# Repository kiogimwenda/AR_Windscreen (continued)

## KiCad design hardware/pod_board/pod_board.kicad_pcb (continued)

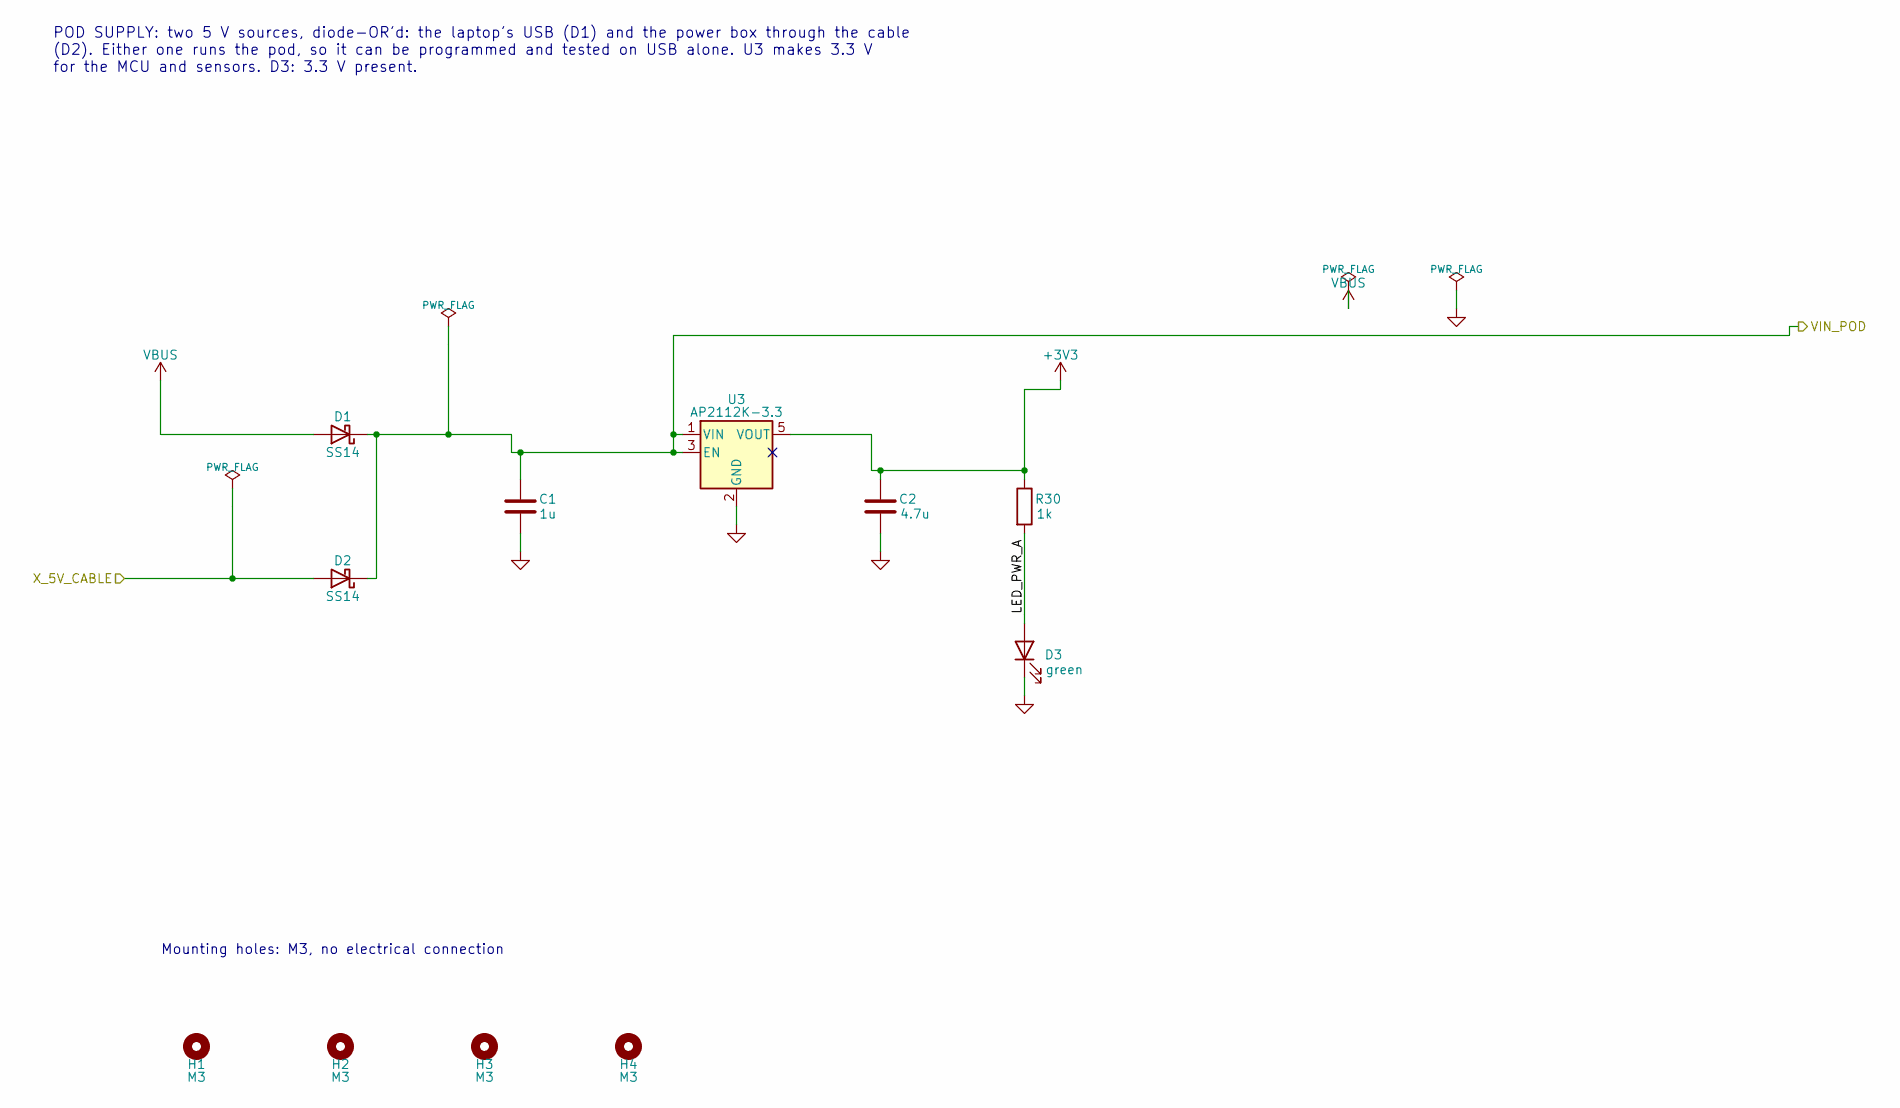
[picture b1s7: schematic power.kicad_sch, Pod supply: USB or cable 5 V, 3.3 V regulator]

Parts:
C1: 1u; C_1206_3216Metric
C2: 4.7u; C_1206_3216Metric
D1, D2: SS14; D_SMA
D3: green; LED_0805_2012Metric
H1, H2, H3, H4: M3; MountingHole_3.2mm_M3
R30: 1k; R_0805_2012Metric
U3: AP2112K-3.3; SOT-23-5

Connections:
+3V3: C2.1, R30.1, U3.5 (VOUT); also elsewhere on the board
/Pod supply: USB or cable 5 V, 3.3 V regulator/LED_PWR_A: D3.2 (A), R30.2
/VIN_POD: C1.1, D1.1 (K), D2.1 (K), U3.1 (VIN), U3.3 (EN); also elsewhere on the board
/X_5V_CABLE: D2.2 (A); also elsewhere on the board
GND: C1.2, C2.2, D3.1 (K), U3.2 (GND); also elsewhere on the board
VBUS: D1.2 (A); also elsewhere on the board

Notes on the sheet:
POD SUPPLY: two 5 V sources, diode-OR'd: the laptop's USB (D1) and the power box through the cable (D2). Either one runs the pod, so it can be programmed and tested on USB alone. U3 makes 3.3 V for the MCU and sensors. D3: 3.3 V present.
Mounting holes: M3, no electrical connection

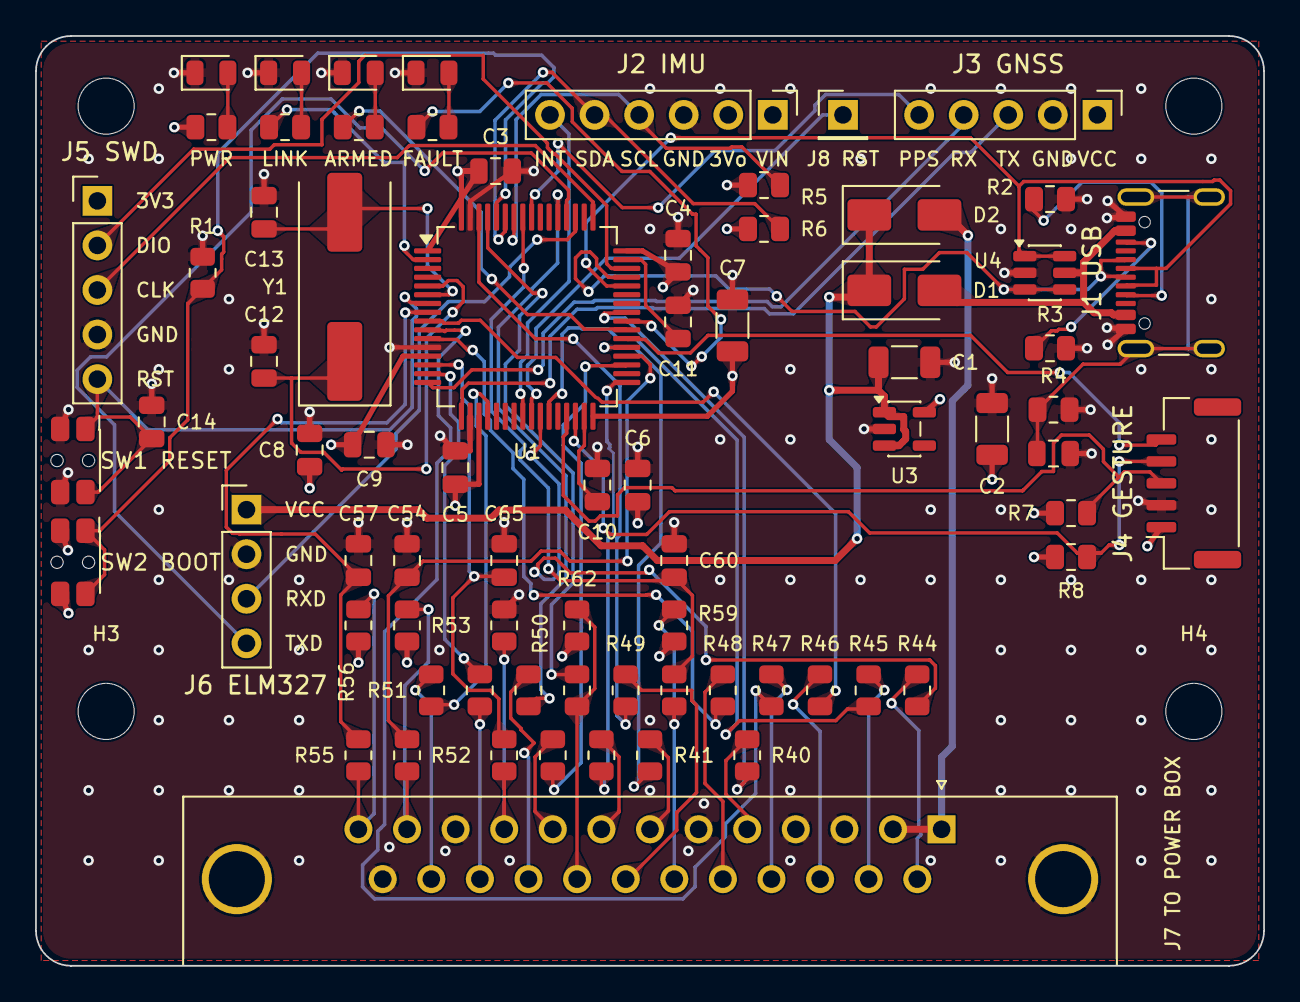
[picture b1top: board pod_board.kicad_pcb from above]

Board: 4 copper layers, 70.0 x 53.0 mm, 78 parts (0 on the bottom side), 73 nets.

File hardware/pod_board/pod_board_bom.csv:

"Reference","Value","Footprint","QUANTITY","Description"
"C1","1u","Capacitor_SMD:C_1206_3216Metric","1","1 uF, not more: USB attach inrush (hardware/sim/run_pod_supply.sh)"
"C2,C7","4.7u","Capacitor_SMD:C_1206_3216Metric","2","4.7 uF, not more: USB attach inrush (hardware/sim/run_pod_supply.sh),bulk, beside the MCU"
"C3-C6,C9,C14,C65","100n","Capacitor_SMD:C_0805_2012Metric","7","VDDA"
"C8","1u","Capacitor_SMD:C_0805_2012Metric","1","VDDA"
"C10,C11","2.2u","Capacitor_SMD:C_0805_2012Metric","2","core regulator, low-ESR ceramic"
"C12,C13","15p","Capacitor_SMD:C_0805_2012Metric","2","crystal load"
"C15","4.7n","Capacitor_SMD:C_0805_2012Metric","1",""
"C54,C57,C60","10n","Capacitor_SMD:C_0805_2012Metric","3",""
"D1,D2","SS14","Diode_SMD:D_SMA","2","+5 V from the power box into the pod's supply (diode-OR),USB VBUS into the pod's supply (diode-OR)"
"D3","green","LED_SMD:LED_0805_2012Metric","1",""
"D4","blue","LED_SMD:LED_0805_2012Metric","1",""
"D5","amber","LED_SMD:LED_0805_2012Metric","1",""
"D6","red","LED_SMD:LED_0805_2012Metric","1",""
"H1-H4","M3","MountingHole:MountingHole_3.2mm_M3","4",""
"J1","USB-C","Connector_USB:USB_C_Receptacle_GCT_USB4105-xx-A_16P_TopMnt_Horizontal","1","to the laptop: the Part 3 protocol; also powers the pod when the cable is out"
"J2","IMU (BNO085 breakout)","Connector_PinHeader_2.54mm:PinHeader_1x06_P2.54mm_Vertical","1","Adafruit 4754 JP1 row: VIN 3Vo(open) GND SCL SDA INT; mount the breakout rigidly"
"J3","GNSS (NEO-M8N breakout)","Connector_PinHeader_2.54mm:PinHeader_1x05_P2.54mm_Vertical","1","MCU GPS_TX goes to the module's RX: names are the MCU's view. Match the breakout's pin order before layout"
"J4","Gesture puck (JST-GH)","Connector_JST:JST_GH_SM05B-GHS-TB_1x05-1MP_P1.25mm_Horizontal","1","APDS-9960 on its own ~1.5 m cable, I2C2 at 100 kHz"
"J5","SWD (ST-Link)","Connector_PinHeader_2.54mm:PinHeader_1x05_P2.54mm_Vertical","1",""
"J6","ELM327 fallback (USART3)","Connector_PinHeader_2.54mm:PinHeader_1x04_P2.54mm_Vertical","1","HC-05 bridge to a Bluetooth ELM327, env:hub_elm327 only (Part 4.8.5); VCC is the pod's 5 V"
"J7","DB-25 to power box","Connector_Dsub:DSUB-25_Socket_Horizontal_P2.77x2.84mm_EdgePinOffset4.94mm_Housed_MountingHolesOffset4.94mm","1","inter-box cable, BUILD_GUIDE 4.8.3"
"J8","IMU reset (optional wire)","Connector_PinHeader_2.54mm:PinHeader_1x01_P2.54mm_Vertical","1","optional jumper to the BNO085 breakout's RST (JP2 pin 4)"
"R1,R53,R56,R59,R62","10k","Resistor_SMD:R_0805_2012Metric","5","BOOT0 low: run from flash,pull-up: the safe reading when the cable is out"
"R2,R3","5.1k","Resistor_SMD:R_0805_2012Metric","2","identifies a USB-C sink: the laptop supplies 5 V"
"R4","1M","Resistor_SMD:R_0805_2012Metric","1",""
"R5,R6","4.7k","Resistor_SMD:R_0805_2012Metric","2",""
"R7,R8","2.2k","Resistor_SMD:R_0805_2012Metric","2","stronger pull-up for the cable"
"R30-R33,R40-R48,R50-R52,R55,R58,R64","1k","Resistor_SMD:R_0805_2012Metric","19","series, DB-25 pin 12,series, DB-25 pin 13,series, DB-25 pin 14,series, DB-25 pin 15,series, DB-25 pin 16,series, DB-25 pin 17,series, DB-25 pin 18,series, DB-25 pin 19,series, DB-25 pin 22,series, DB-25 pin 24,series, DB-25 pin 5,series, DB-25 pin 7,series, DB-25 pin 8,series, DB-25 pin 9"
"R49","330","Resistor_SMD:R_0805_2012Metric","1","series, DB-25 pin 20"
"R61,R63","100","Resistor_SMD:R_0805_2012Metric","2","series, DB-25 pin 21,series, DB-25 pin 23"
"R66","100k","Resistor_SMD:R_0805_2012Metric","1","defined reading (0 V) when the cable is out; firmware ignores it then"
"SW1","RESET","Button_Switch_SMD:SW_SPST_EVQP7C","1",""
"SW2","BOOT","Button_Switch_SMD:SW_SPST_EVQP7C","1","hold at reset for the USB DFU bootloader"
"U1","STM32F405RGT6","Package_QFP:LQFP-64_10x10mm_P0.5mm","1",""
"U3","AP2112K-3.3","Package_TO_SOT_SMD:SOT-23-5","1","3.3 V, 600 mA LDO"
"U4","USBLC6-2SC6","Package_TO_SOT_SMD:SOT-23-6","1","USB ESD protection"
"Y1","8MHz","Crystal:Crystal_SMD_HC49-SD","1","HSE; firmware assumes 8 MHz (HSE_VALUE). Load caps for CL = 10 pF."

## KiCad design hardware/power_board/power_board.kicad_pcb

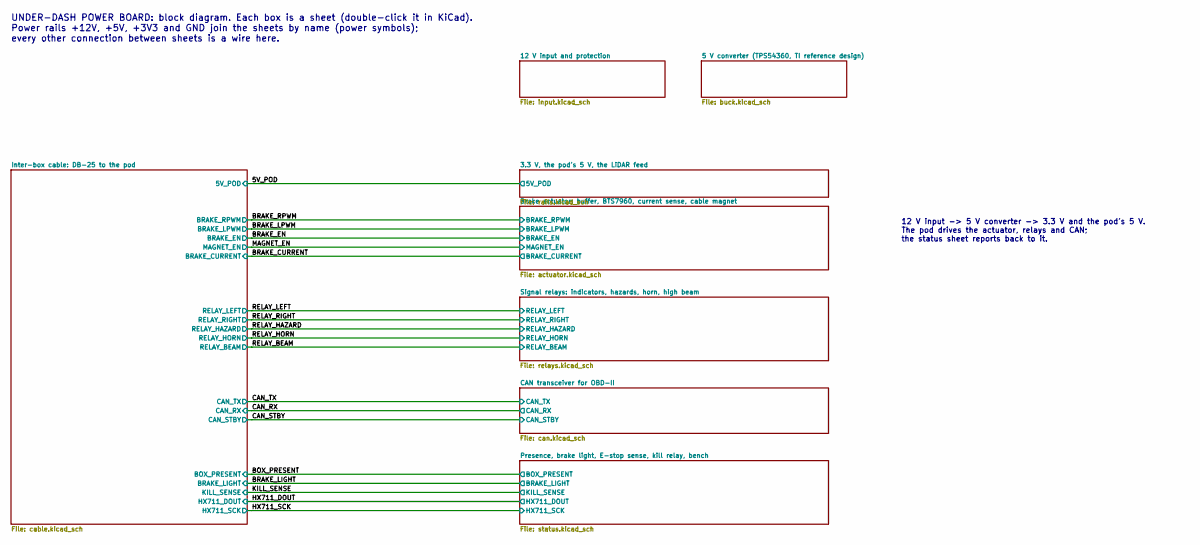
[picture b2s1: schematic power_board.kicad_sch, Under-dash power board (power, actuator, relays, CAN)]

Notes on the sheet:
UNDER-DASH POWER BOARD: block diagram. Each box is a sheet (double-click it in KiCad). Power rails +12V, +5V, +3V3 and GND join the sheets by name (power symbols); every other connection between sheets is a wire here.
12 V input -> 5 V converter -> 3.3 V and the pod's 5 V. The pod drives the actuator, relays and CAN; the status sheet reports back to it.

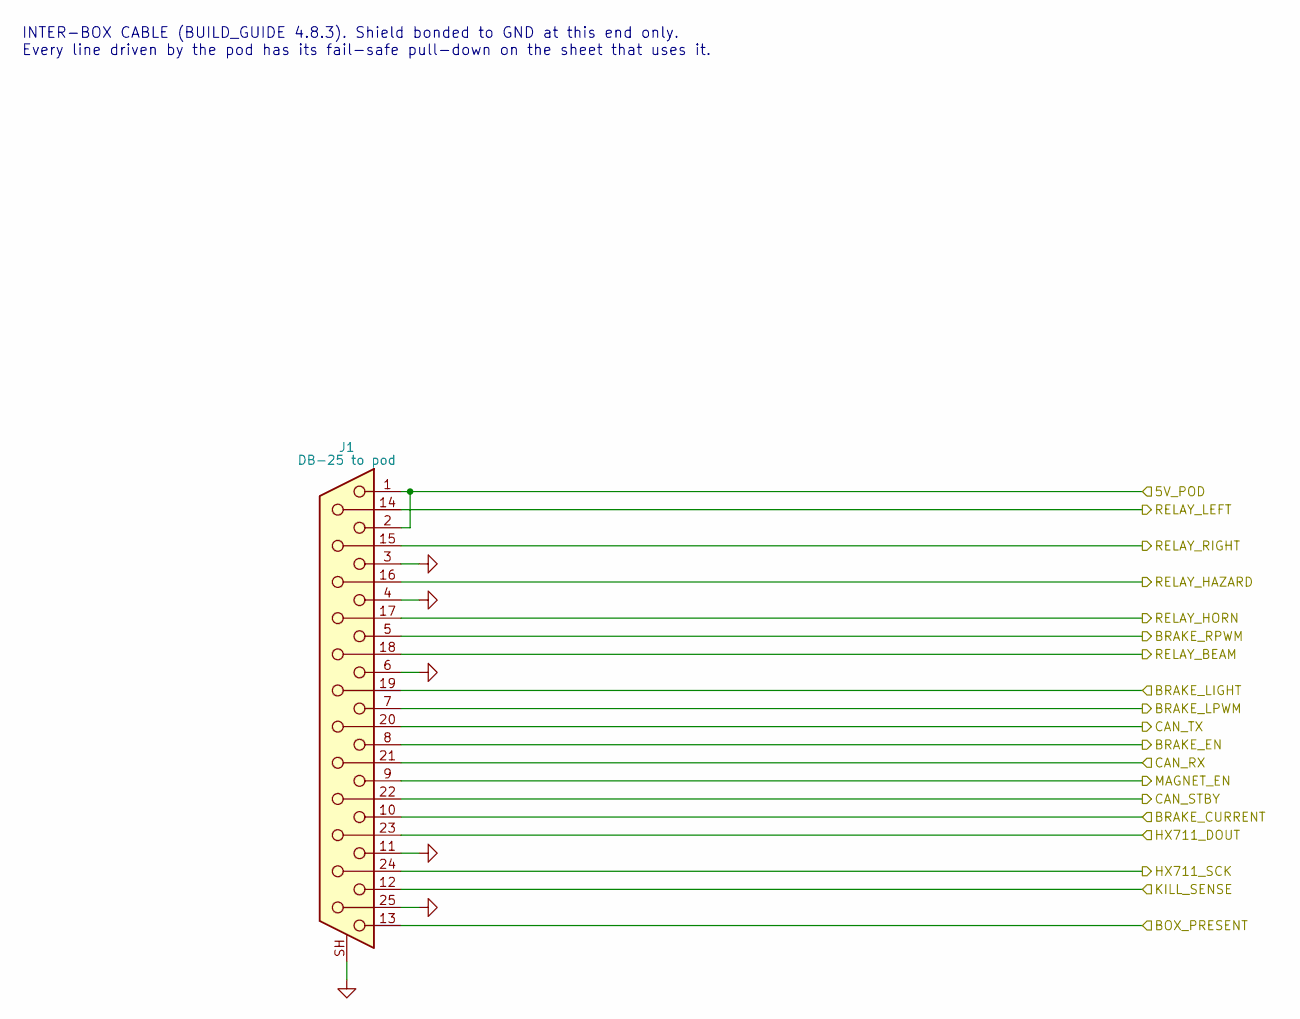
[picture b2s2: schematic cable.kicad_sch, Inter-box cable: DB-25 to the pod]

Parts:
J1: DB-25 to pod; DSUB-25_Socket_Horizontal_P2.77x2.84mm_EdgePinOffset4.94mm_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

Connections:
/5V_POD: J1.1, J1.2; also elsewhere on the board
/BOX_PRESENT: J1.13; also elsewhere on the board
/BRAKE_CURRENT: J1.10; also elsewhere on the board
/BRAKE_EN: J1.8; also elsewhere on the board
/BRAKE_LIGHT: J1.19; also elsewhere on the board
/BRAKE_LPWM: J1.7; also elsewhere on the board
/BRAKE_RPWM: J1.5; also elsewhere on the board
/CAN_RX: J1.21; also elsewhere on the board
/CAN_STBY: J1.22; also elsewhere on the board
/CAN_TX: J1.20; also elsewhere on the board
/HX711_DOUT: J1.23; also elsewhere on the board
/HX711_SCK: J1.24; also elsewhere on the board
/KILL_SENSE: J1.12; also elsewhere on the board
/MAGNET_EN: J1.9; also elsewhere on the board
/RELAY_BEAM: J1.18; also elsewhere on the board
/RELAY_HAZARD: J1.16; also elsewhere on the board
/RELAY_HORN: J1.17; also elsewhere on the board
/RELAY_LEFT: J1.14; also elsewhere on the board
/RELAY_RIGHT: J1.15; also elsewhere on the board
GND: J1.3, J1.4, J1.6, J1.11, J1.25, J1.SH (PAD); also elsewhere on the board

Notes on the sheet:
INTER-BOX CABLE (BUILD_GUIDE 4.8.3). Shield bonded to GND at this end only. Every line driven by the pod has its fail-safe pull-down on the sheet that uses it.

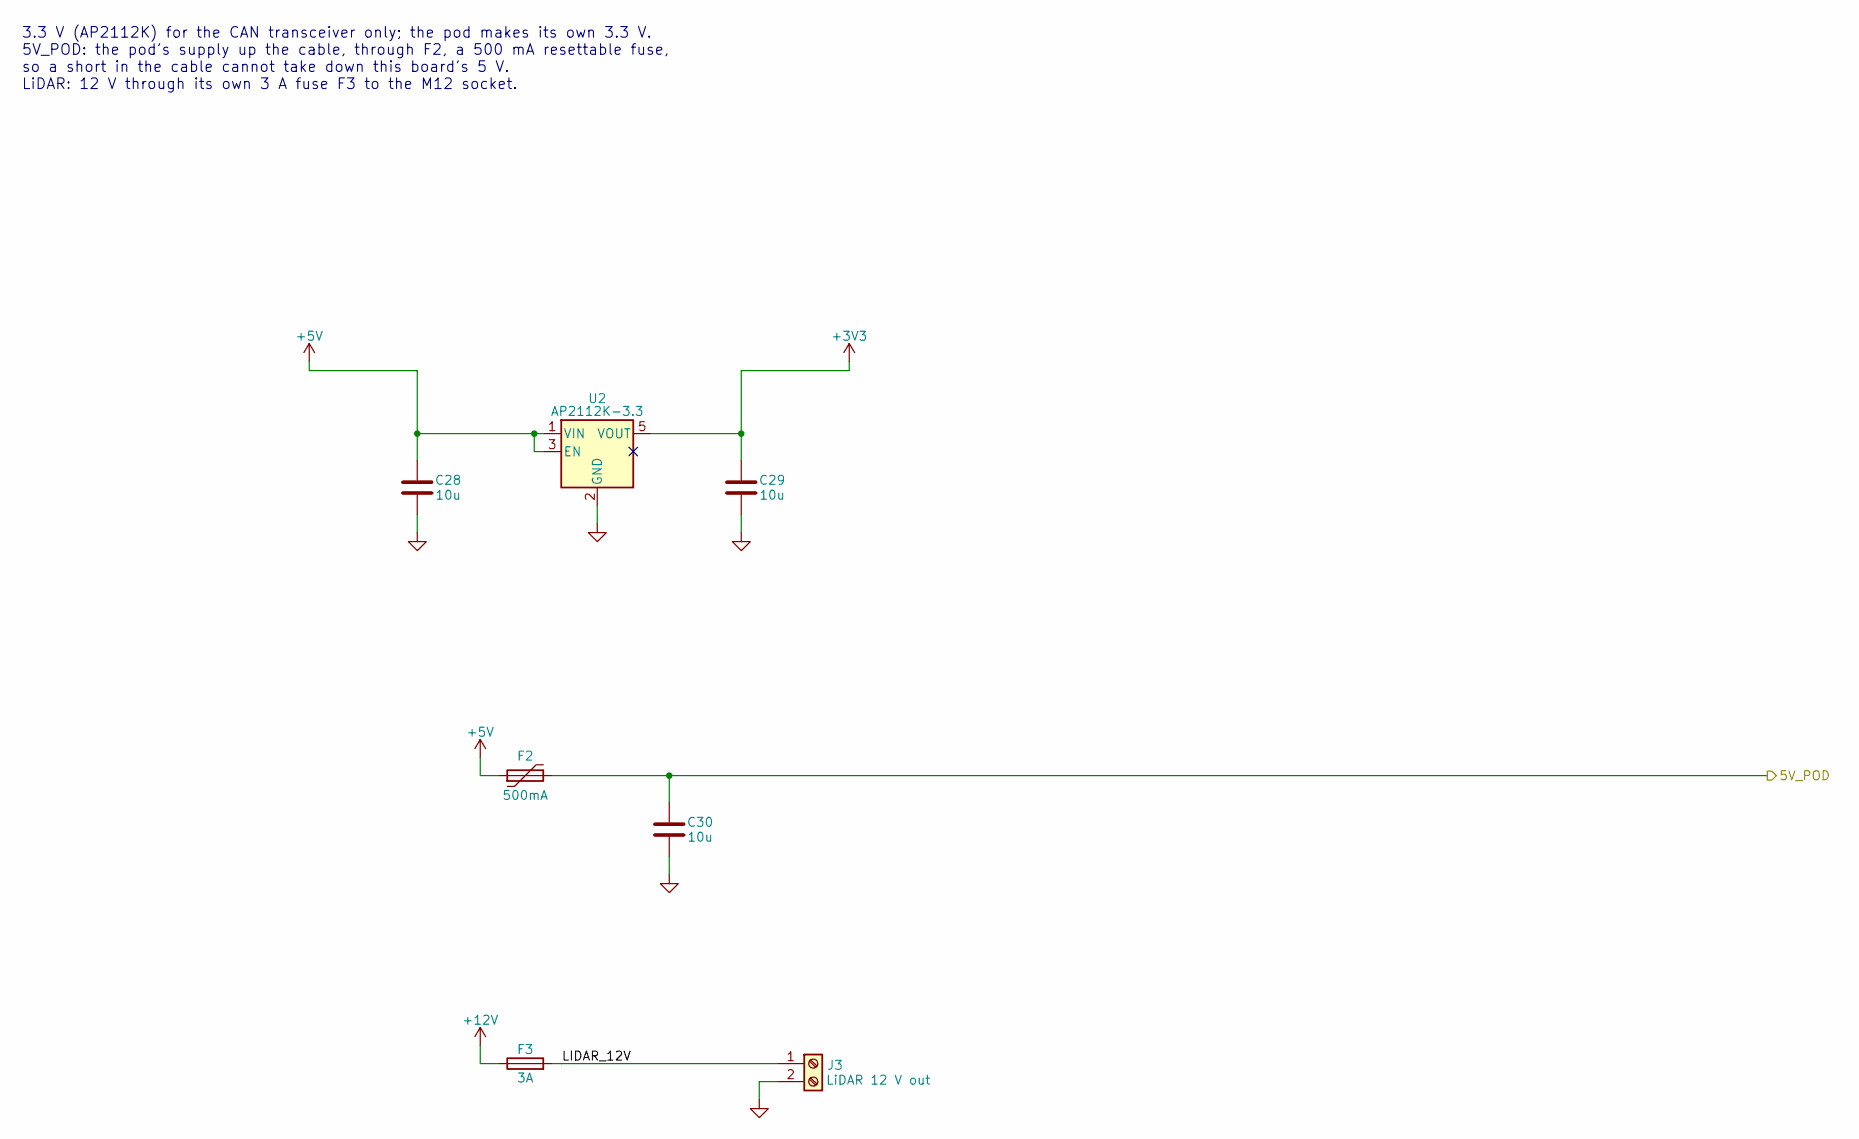
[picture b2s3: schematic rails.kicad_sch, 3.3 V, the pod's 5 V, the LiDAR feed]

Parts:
C28, C29, C30: 10u; C_1206_3216Metric
F2: 500mA; Fuse_1206_3216Metric
F3: 3A; Fuseholder_Blade_Mini_Keystone_3568
J3: LiDAR 12 V out; TerminalBlock_Phoenix_MKDS-1,5-2-5.08_1x02_P5.08mm_Horizont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
U2: AP2112K-3.3; SOT-23-5

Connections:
+3V3: C29.1, U2.5 (VOUT); also elsewhere on the board
+5V: C28.1, F2.1, U2.1 (VIN), U2.3 (EN); also elsewhere on the board
+12V: F3.1; also elsewhere on the board
/3.3 V, the pod's 5 V, the LiDAR feed/LIDAR_12V: F3.2, J3.1
/5V_POD: C30.1, F2.2; also elsewhere on the board
GND: C28.2, C29.2, C30.2, J3.2, U2.2 (GND); also elsewhere on the board

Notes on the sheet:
3.3 V (AP2112K) for the CAN transceiver only; the pod makes its own 3.3 V. 5V_POD: the pod's supply up the cable, through F2, a 500 mA resettable fuse, so a short in the cable cannot take down this board's 5 V. LiDAR: 12 V through its own 3 A fuse F3 to the M12 socket.

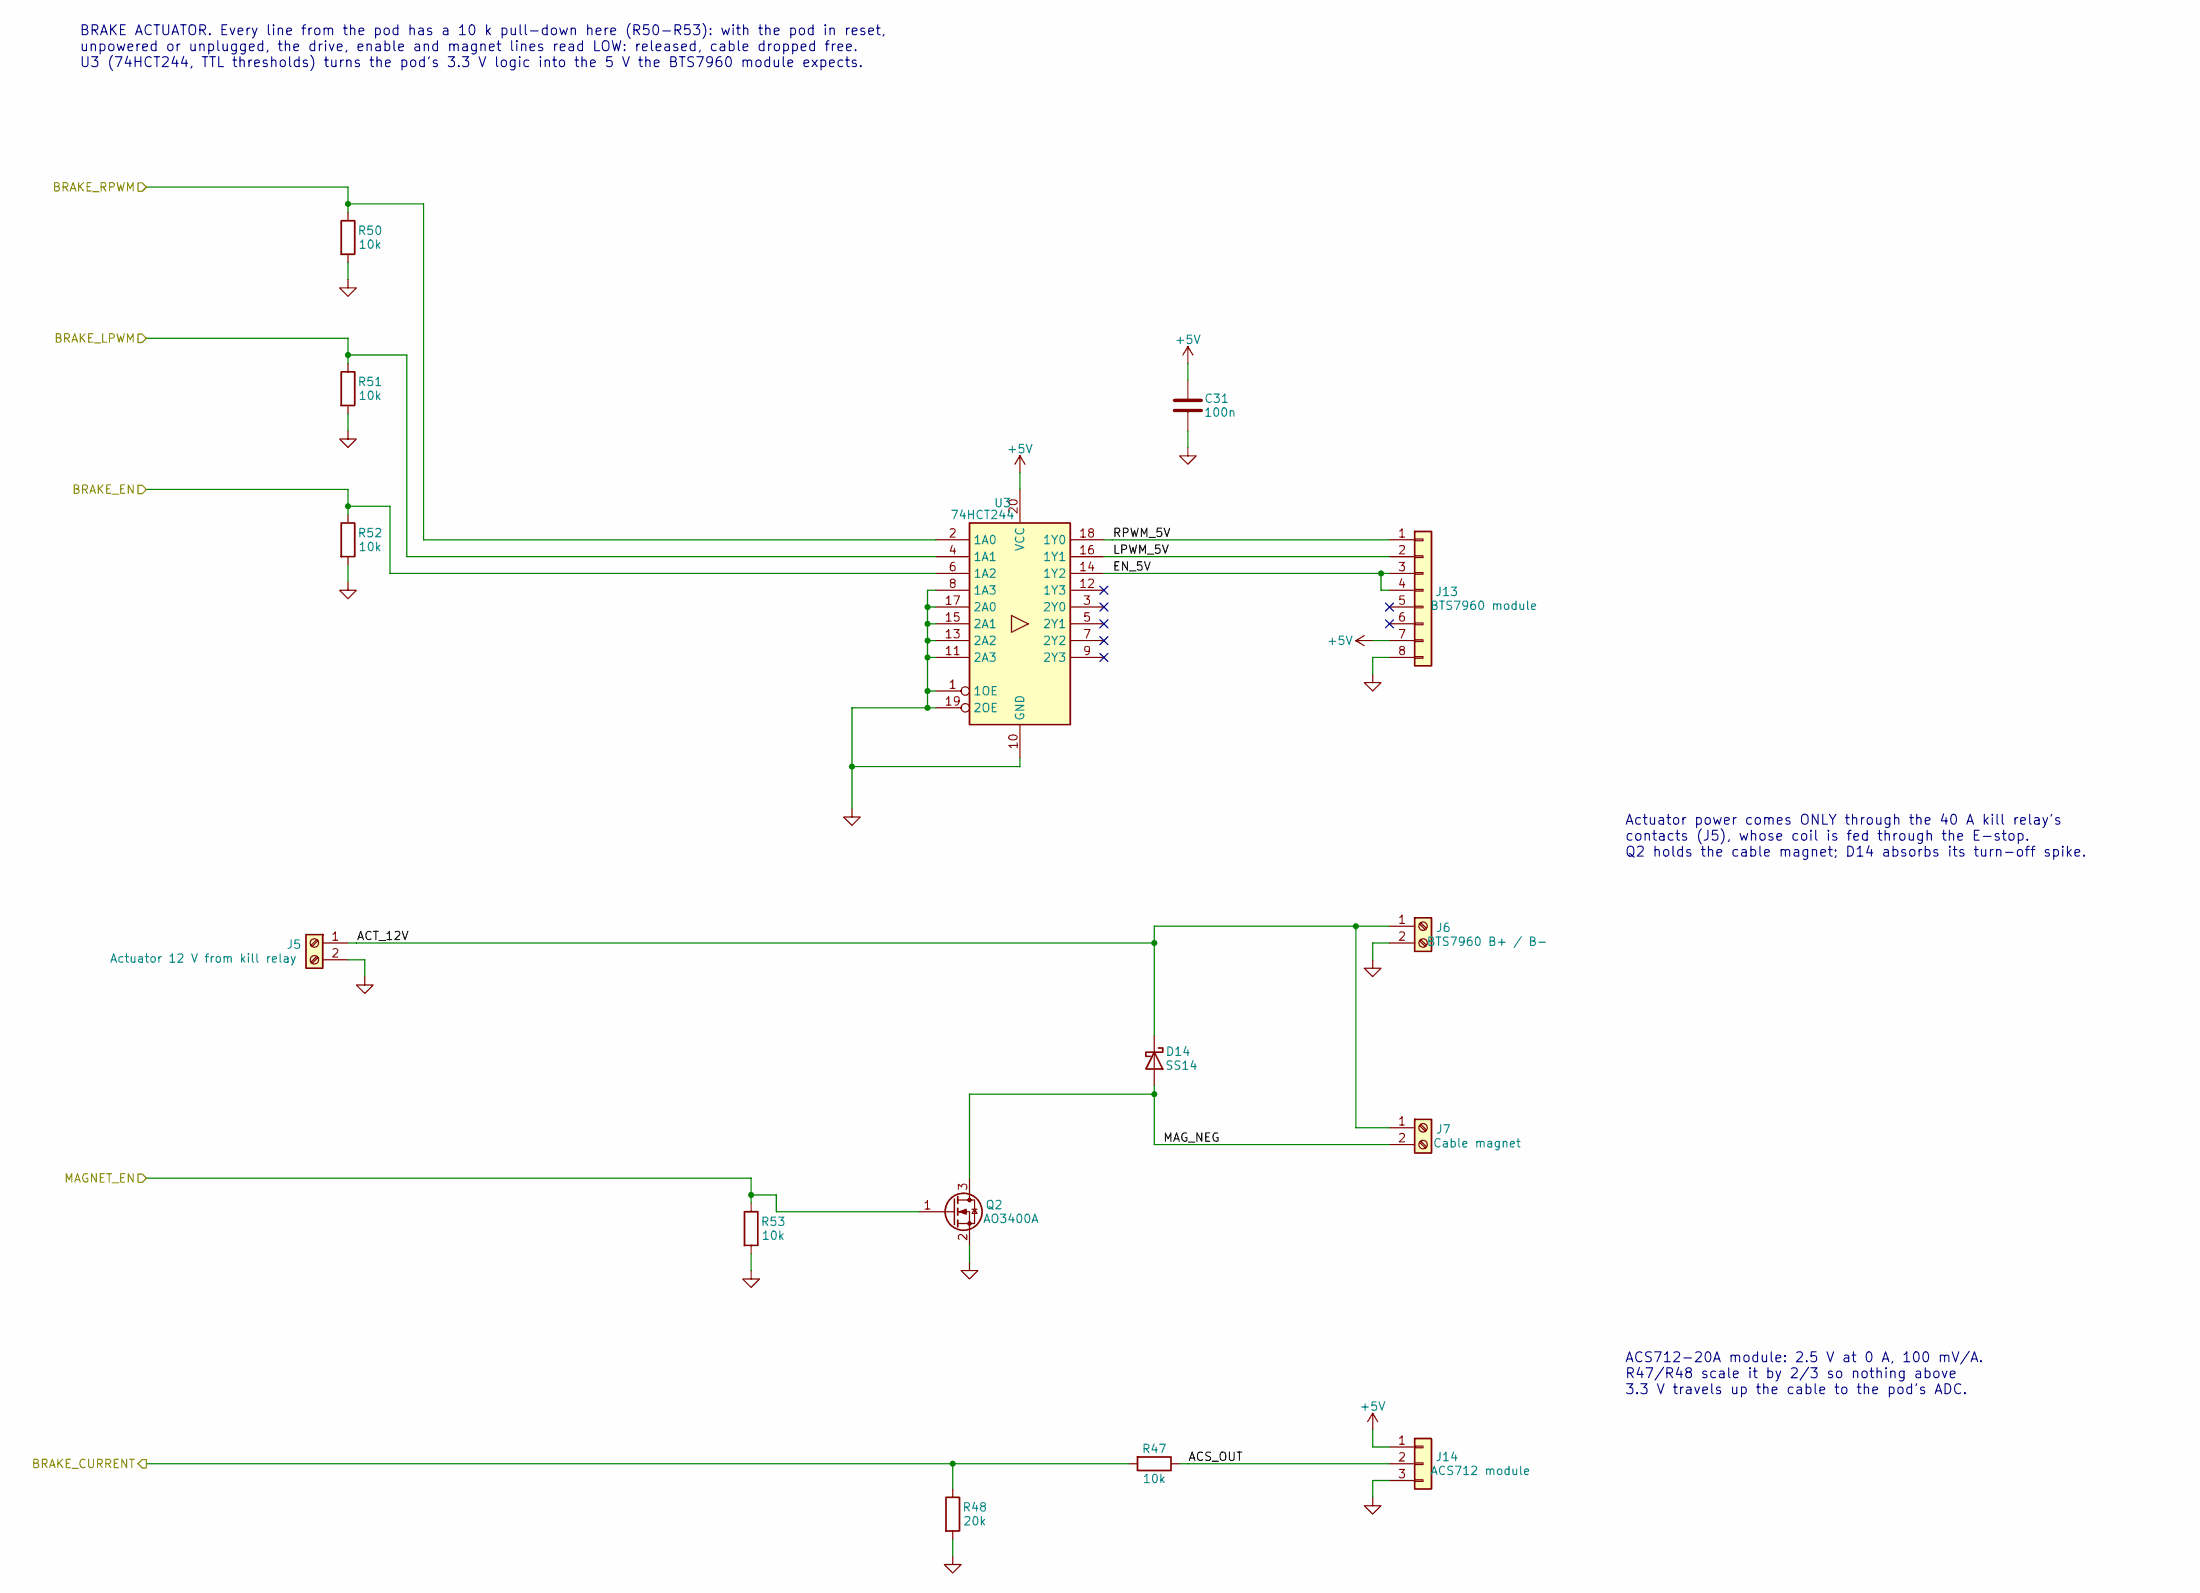
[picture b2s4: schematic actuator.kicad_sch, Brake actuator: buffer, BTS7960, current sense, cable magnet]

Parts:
C31: 100n; C_0805_2012Metric
D14: SS14; D_SMA
J5: Actuator 12 V from kill relay; TerminalBlock_Phoenix_MKDS-1,5-2-5.08_1x02_P5.08mm_Horizont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
J6: BTS7960 B+ / B-; TerminalBlock_Phoenix_MKDS-1,5-2-5.08_1x02_P5.08mm_Horizont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
J7: Cable magnet; TerminalBlock_Phoenix_MKDS-1,5-2-5.08_1x02_P5.08mm_Horizont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
J13: BTS7960 module; PinHeader_1x08_P2.54mm_Vertical
J14: ACS712 module; PinHeader_1x03_P2.54mm_Vertical
Q2: AO3400A; SOT-23
R47, R50, R51, R52, R53: 10k; R_0805_2012Metric
R48: 20k; R_0805_2012Metric
U3: 74HCT244; SOIC-20W_7.5x12.8mm_P1.27mm

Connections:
+5V: C31.1, J13.7, J14.1, U3.20 (VCC); also elsewhere on the board
/BRAKE_CURRENT: R47.2, R48.1; also elsewhere on the board
/BRAKE_EN: R52.1, U3.6 (1A2); also elsewhere on the board
/BRAKE_LPWM: R51.1, U3.4 (1A1); also elsewhere on the board
/BRAKE_RPWM: R50.1, U3.2 (1A0); also elsewhere on the board
/Brake actuator: buffer, BTS7960, current sense, cable magnet/ACS_OUT: J14.2, R47.1
/Brake actuator: buffer, BTS7960, current sense, cable magnet/ACT_12V: D14.1 (K), J5.1, J6.1, J7.1
/Brake actuator: buffer, BTS7960, current sense, cable magnet/EN_5V: J13.3, J13.4, U3.14 (1Y2)
/Brake actuator: buffer, BTS7960, current sense, cable magnet/LPWM_5V: J13.2, U3.16 (1Y1)
/Brake actuator: buffer, BTS7960, current sense, cable magnet/MAG_NEG: D14.2 (A), J7.2, Q2.3 (D)
/Brake actuator: buffer, BTS7960, current sense, cable magnet/RPWM_5V: J13.1, U3.18 (1Y0)
/MAGNET_EN: Q2.1 (G), R53.1; also elsewhere on the board
GND: C31.2, J5.2, J6.2, J13.8, J14.3, Q2.2 (S), R48.2, R50.2, R51.2, R52.2, R53.2, U3.1 (1OE), U3.8 (1A3), U3.10 (GND), U3.11 (2A3), U3.13 (2A2), U3.15 (2A1), U3.17 (2A0), U3.19 (2OE); also elsewhere on the board

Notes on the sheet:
BRAKE ACTUATOR. Every line from the pod has a 10 k pull-down here (R50-R53): with the pod in reset, unpowered or unplugged, the drive, enable and magnet lines read LOW: released, cable dropped free. U3 (74HCT244, TTL thresholds) turns the pod's 3.3 V logic into the 5 V the BTS7960 module expects.
Actuator power comes ONLY through the 40 A kill relay's contacts (J5), whose coil is fed through the E-stop. Q2 holds the cable magnet; D14 absorbs its turn-off spike.
ACS712-20A module: 2.5 V at 0 A, 100 mV/A. R47/R48 scale it by 2/3 so nothing above 3.3 V travels up the cable to the pod's ADC.

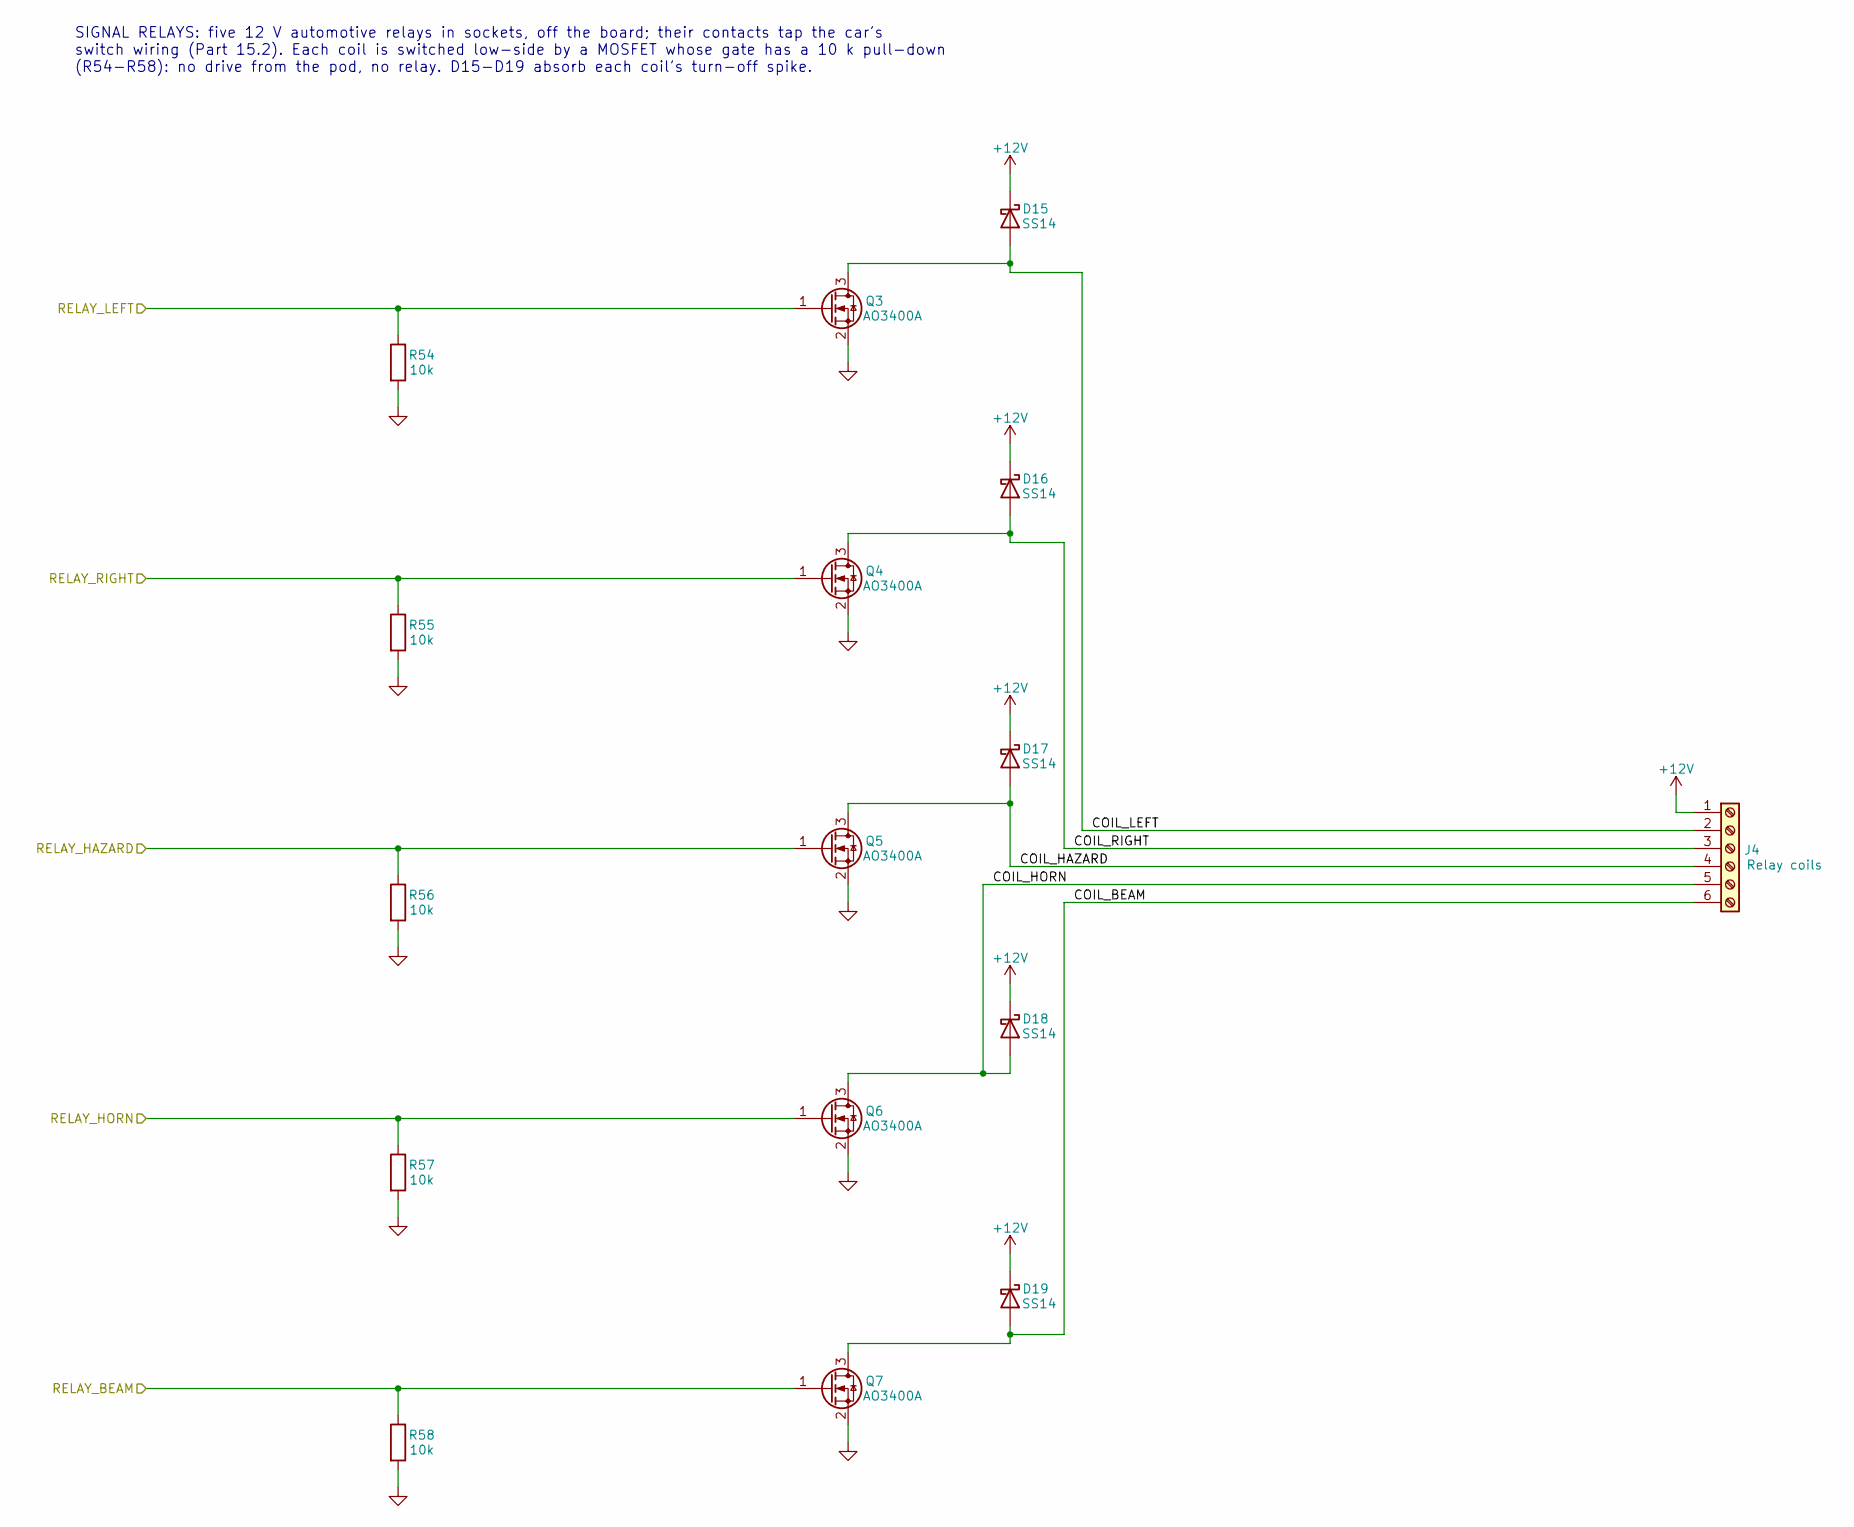
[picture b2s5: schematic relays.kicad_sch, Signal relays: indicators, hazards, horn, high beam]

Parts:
D15, D16, D17, D18, D19: SS14; D_SMA
J4: Relay coils; TerminalBlock_Phoenix_MKDS-1,5-6-5.08_1x06_P5.08mm_Horizont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
Q3, Q4, Q5, Q6, Q7: AO3400A; SOT-23
R54, R55, R56, R57, R58: 10k; R_0805_2012Metric

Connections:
+12V: D15.1 (K), D16.1 (K), D17.1 (K), D18.1 (K), D19.1 (K), J4.1; also elsewhere on the board
/RELAY_BEAM: Q7.1 (G), R58.1; also elsewhere on the board
/RELAY_HAZARD: Q5.1 (G), R56.1; also elsewhere on the board
/RELAY_HORN: Q6.1 (G), R57.1; also elsewhere on the board
/RELAY_LEFT: Q3.1 (G), R54.1; also elsewhere on the board
/RELAY_RIGHT: Q4.1 (G), R55.1; also elsewhere on the board
/Signal relays: indicators, hazards, horn, high beam/COIL_BEAM: D19.2 (A), J4.6, Q7.3 (D)
/Signal relays: indicators, hazards, horn, high beam/COIL_HAZARD: D17.2 (A), J4.4, Q5.3 (D)
/Signal relays: indicators, hazards, horn, high beam/COIL_HORN: D18.2 (A), J4.5, Q6.3 (D)
/Signal relays: indicators, hazards, horn, high beam/COIL_LEFT: D15.2 (A), J4.2, Q3.3 (D)
/Signal relays: indicators, hazards, horn, high beam/COIL_RIGHT: D16.2 (A), J4.3, Q4.3 (D)
GND: Q3.2 (S), Q4.2 (S), Q5.2 (S), Q6.2 (S), Q7.2 (S), R54.2, R55.2, R56.2, R57.2, R58.2; also elsewhere on the board

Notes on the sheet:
SIGNAL RELAYS: five 12 V automotive relays in sockets, off the board; their contacts tap the car's switch wiring (Part 15.2). Each coil is switched low-side by a MOSFET whose gate has a 10 k pull-down (R54-R58): no drive from the pod, no relay. D15-D19 absorb each coil's turn-off spike.

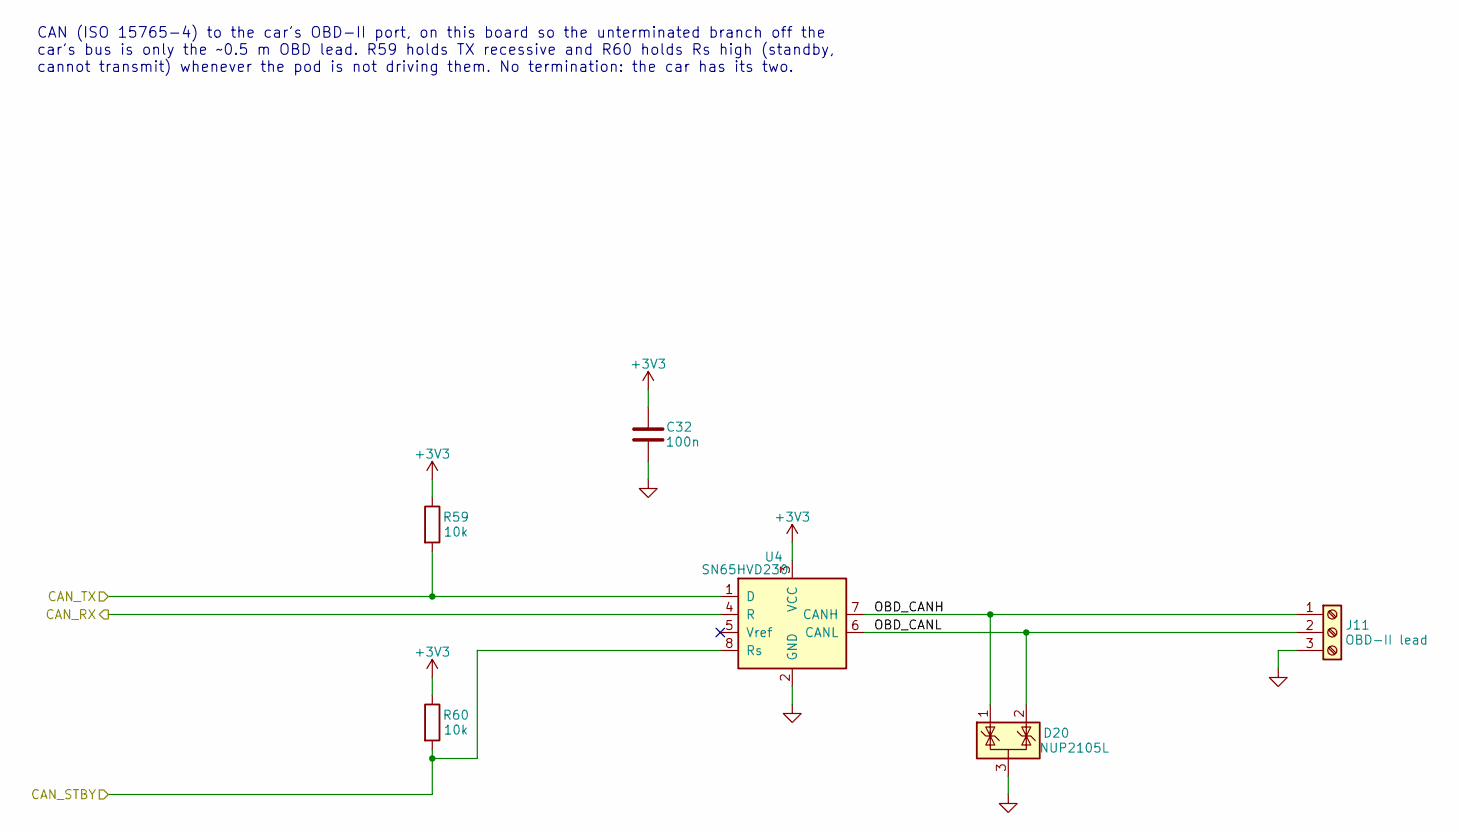
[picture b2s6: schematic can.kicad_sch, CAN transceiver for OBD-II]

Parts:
C32: 100n; C_0805_2012Metric
D20: NUP2105L; SOT-23
J11: OBD-II lead; TerminalBlock_Phoenix_MKDS-1,5-3-5.08_1x03_P5.08mm_Horizont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
R59, R60: 10k; R_0805_2012Metric
U4: SN65HVD230; SOIC-8_3.9x4.9mm_P1.27mm

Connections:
+3V3: C32.1, R59.1, R60.1, U4.3 (VCC); also elsewhere on the board
/CAN transceiver for OBD-II/OBD_CANH: D20.1 (K), J11.1, U4.7 (CANH)
/CAN transceiver for OBD-II/OBD_CANL: D20.2 (K), J11.2, U4.6 (CANL)
/CAN_RX: U4.4 (R); also elsewhere on the board
/CAN_STBY: R60.2, U4.8 (Rs); also elsewhere on the board
/CAN_TX: R59.2, U4.1 (D); also elsewhere on the board
GND: C32.2, D20.3 (A), J11.3, U4.2 (GND); also elsewhere on the board

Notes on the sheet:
CAN (ISO 15765-4) to the car's OBD-II port, on this board so the unterminated branch off the car's bus is only the ~0.5 m OBD lead. R59 holds TX recessive and R60 holds Rs high (standby, cannot transmit) whenever the pod is not driving them. No termination: the car has its two.
